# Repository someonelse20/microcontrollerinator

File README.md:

# Microcontrollerinator
Simple custom devboard based on the RP2040 with an integraded 1 cell li-ion charger and Dr. Doofenshmirtz because why not.
This is my first complex pcb and to get my feet wet I mostly followed the example at https://blueprint.hackclub.com/starter-projects/devboard and added the BQ21040DBV battery charger. 

# How To Use
The board has the same pinout as the Raspberry Pi Pico exept ADC_VREF is GPIO23, 3V3_EN is GPIO24, and VSYS is GPIO25. GPIO29_ADC3 monitors the voltage of the battery multiplied by 1.3125 due to the resistor dividor. Pressing the switch will put the RP2040 into boot mode so it can be programed. The VBUS pin will output the current power supply voltage which will be 5v when plugged in but will be the direct battery voltage when unplugged. The battery pin headder has three pins, two for power and one for a thermistor to monitor temperature. The thermistor can be left hanging but there is a solder pad that enables a pull up resistor which is recomended in the charger datasheet.

# Schematic

# PCB

# Ordering
This bom file, the cpl position file, and the gerber zip files are in the production folder and formated to be orederd from https://jlcpcb.com/. The positions file needs to be edited a bit and there isn't an option to export the updated cpl file for JLCPCB so edit as show in the picture below. The USB header goes down a little, U2 pin 1 goes to the bottom left, U3 pin 1 goes to the top left, U4 pin 1 goes to the bottom left, and Q1 pin 1 goes to the top left.
| Id    | Designator                          | Footprint                                   | Quantity | Comment                     | Lcsc part |
| :---- | :---------------------------------- | :------------------------------------------ | :------- | :-------------------------- | :-------- |
| 1     | Y1                                  | Crystal_SMD_3225-4Pin_3.2x2.5mm             | 1        | 12MHz                       | C9002     |
| 2     | SW1                                 | SW_Push_SPST_NO_Alps_SKRK                   | 1        | SW_Push                     | C720477   |
| 3     | C16,C15                             | C_0402_1005Metric                           | 2        | 33pF                        | C1562     |
| 4     | C5,C3,C4,C8,C2,C11,C9,C12,C6,C7,C17 | C_0402_1005Metric                           | 11       | 0.1uF                       | C1525     |
| 5     | J4,J5                               | PinHeader_1x03_P2.54mm_Vertical             | 2        | Conn_01x03                  |           |
| 6     | R6,R11,R9,R5                        | R_0402_1005Metric                           | 4        | 1K                          | C11702    |
| 7     | R2,R1                               | R_0402_1005Metric                           | 2        | 5.1K                        | C25905    |
| 8     | U2                                  | SOT-23                                      | 1        | MCP1700x-330xxTT            | C39051    |
| 9     | C14,C13                             | C_0603_1608Metric                           | 2        | 10uF                        | C19702    |
| 10    | C10,C1,C19,C18                      | C_0402_1005Metric                           | 4        | 1uF                         | C52923    |
| 11    | J1                                  | USB_C_Receptacle_HRO_TYPE-C-31-M-12         | 1        | USB_C_Receptacle_USB2.0_14P | C165948   |
| 12    | U3                                  | Winbond_USON-8-1EP_3x2mm_P0.5mm_EP0.2x1.6mm | 1        | W25Q128JVS                  | C2843335  |
| 13    | D2                                  | LED_0603_1608Metric                         | 1        | LED                         | C2290     |
| 14    | U4                                  | SOT-23-6                                    | 1        | BQ21040DBV                  | C202311   |
| 15    | R8                                  | R_0402_1005Metric                           | 1        | 1.5K                        | C25867    |
| 16    | R12                                 | R_0402_1005Metric                           | 1        | 3.2K                        | C705066   |
| 17    | U1                                  | QFN-56-1EP_7x7mm_P0.4mm_EP3.2x3.2mm         | 1        | RP2040                      | C2040     |
| 18    | D1                                  | D_0402_1005Metric                           | 1        | D_Schottky                  | C28646371 |
| 19    | Q1                                  | SOT-23                                      | 1        | AO3401A                     | C15127    |
| 20    | R4,R3                               | R_0402_1005Metric                           | 2        | 27K                         | C11896    |
| 21    | R10,R7                              | R_0402_1005Metric                           | 2        | 10K                         | C25744    |
| 22    | J3,J2                               | PinHeader_1x20_P2.54mm_Vertical             | 2        | Conn_01x20                  |           |

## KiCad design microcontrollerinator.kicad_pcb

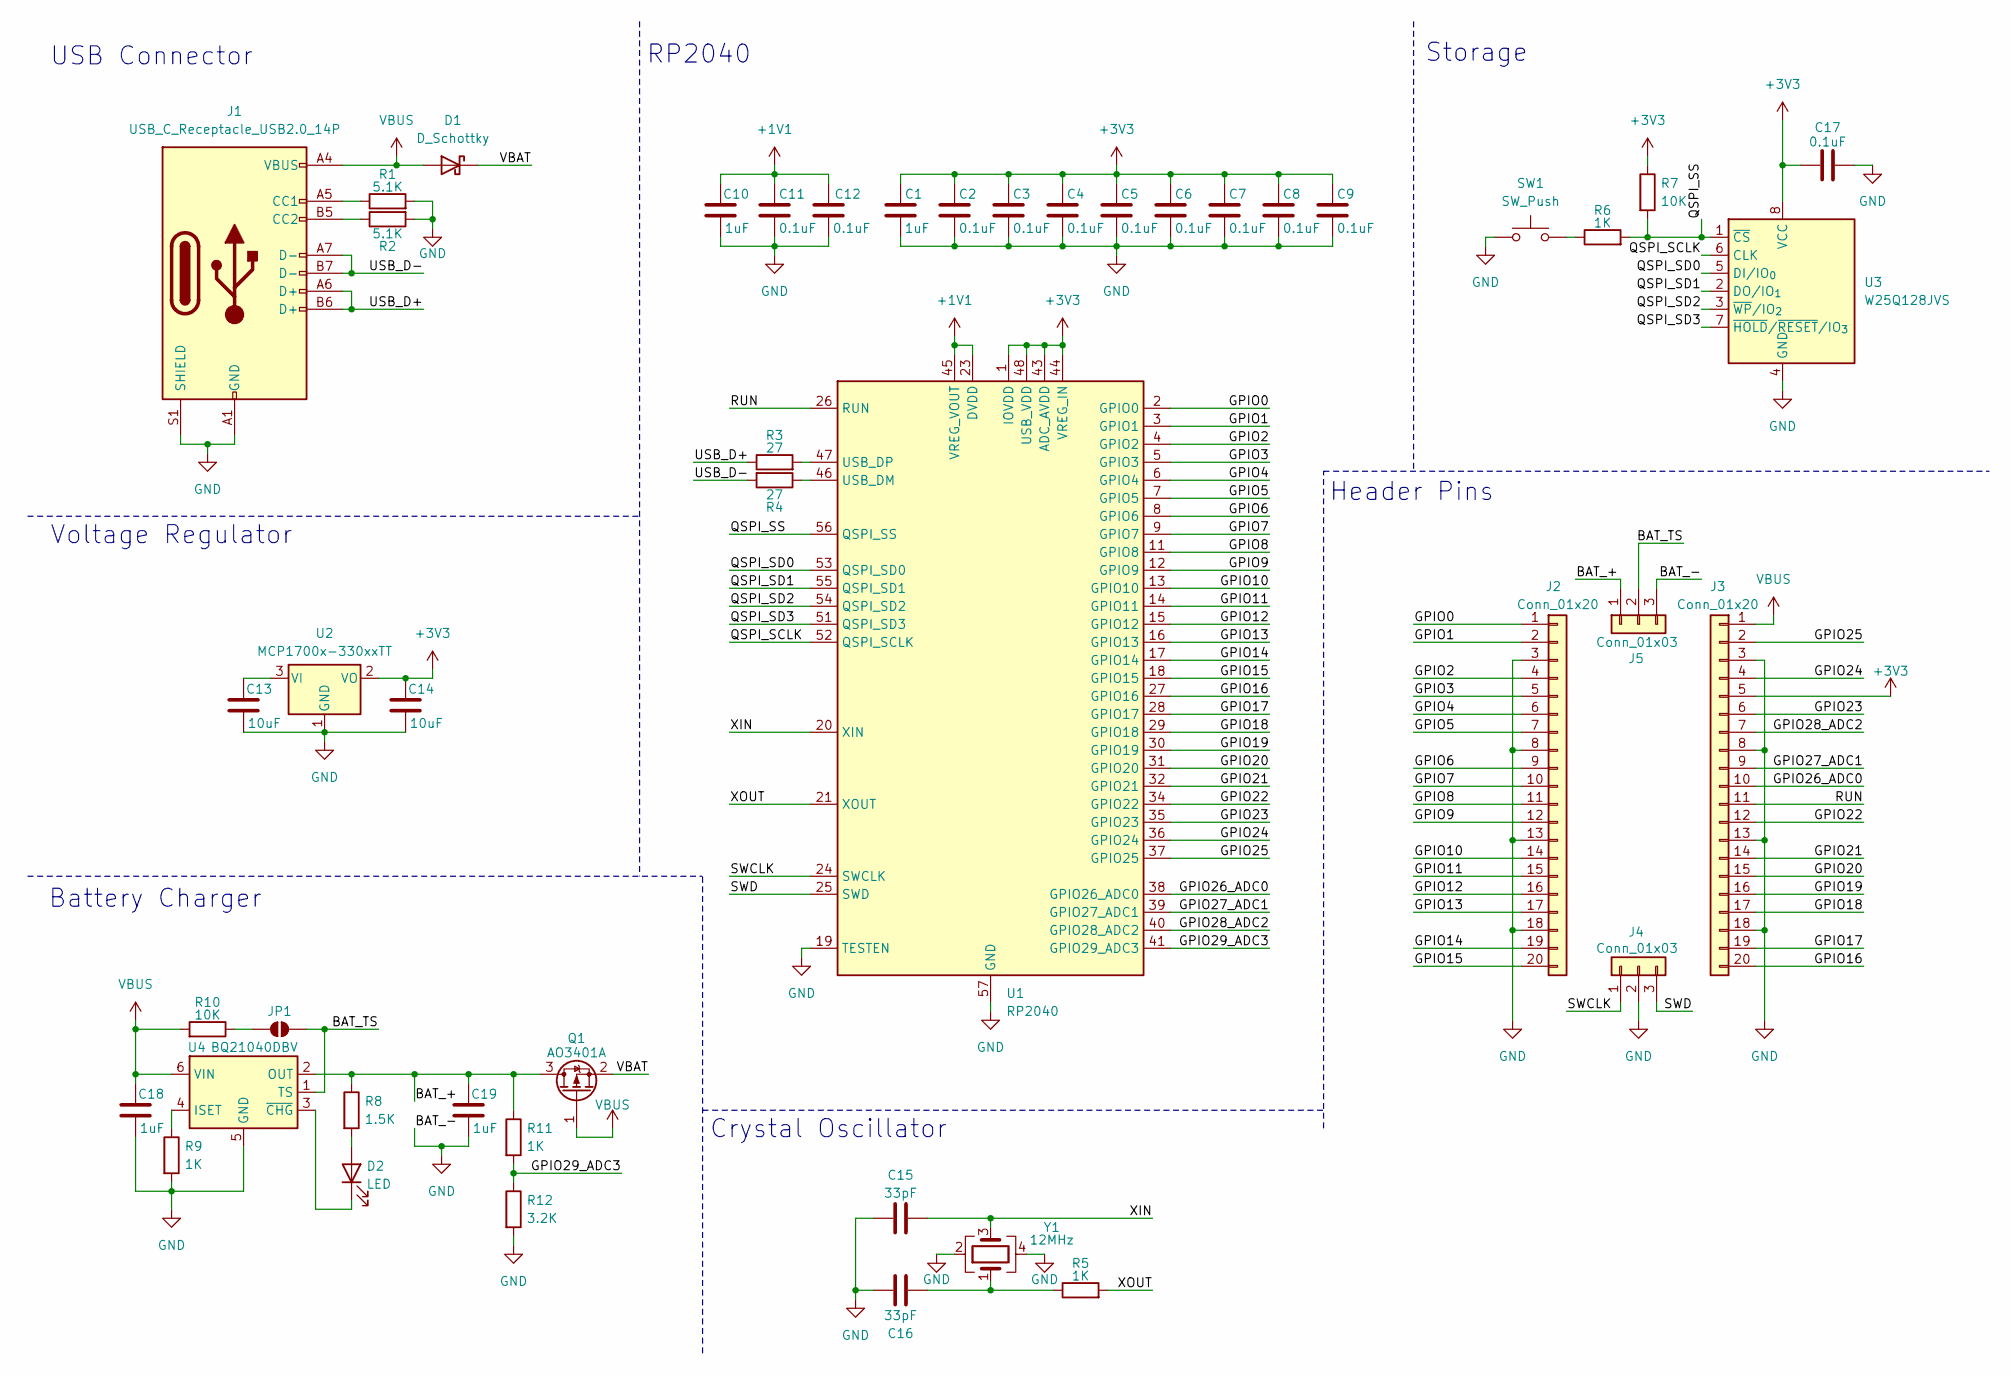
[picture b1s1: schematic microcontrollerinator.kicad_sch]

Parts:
C1, C10, C18, C19: 1uF; C_0402_1005Metric
C2, C3, C4, C5, C6, C7, C8, C9, C11, C12, C17: 0.1uF; C_0402_1005Metric
C13, C14: 10uF; C_0603_1608Metric
C15, C16: 33pF; C_0402_1005Metric
D1: D_Schottky; D_0402_1005Metric
D2: LED; LED_0603_1608Metric
J1: USB_C_Receptacle_USB2.0_14P; USB_C_Receptacle_HRO_TYPE-C-31-M-12
J2, J3: Conn_01x20; PinHeader_1x20_P2.54mm_Vertical
J4, J5: Conn_01x03; PinHeader_1x03_P2.54mm_Vertical
JP1: SolderJumper_2_Open; SolderJumper-2_P1.3mm_Open_RoundedPad1.0x1.5mm
Q1: AO3401A; SOT-23
R1, R2: 5.1K; R_0402_1005Metric
R3, R4: 27; R_0402_1005Metric
R5, R6, R9, R11: 1K; R_0402_1005Metric
R7, R10: 10K; R_0402_1005Metric
R8: 1.5K; R_0402_1005Metric
R12: 3.2K; R_0402_1005Metric
SW1: SW_Push; SW_Push_SPST_NO_Alps_SKRK
U1: RP2040; QFN-56-1EP_7x7mm_P0.4mm_EP3.2x3.2mm
U2: MCP1700x-330xxTT; SOT-23
U3: W25Q128JVS; Winbond_USON-8-1EP_3x2mm_P0.5mm_EP0.2x1.6mm
U4: BQ21040DBV; SOT-23-6
Y1: 12MHz; Crystal_SMD_3225-4Pin_3.2x2.5mm

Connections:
+1V1: C10.1, C11.1, C12.1, U1.23 (DVDD), U1.45 (VREG_VOUT), U1.50 (DVDD)
+3V3: C1.1, C2.1, C3.1, C4.1, C5.1, C6.1, C7.1, C8.1, C9.1, C14.1, C17.1, J3.5, R7.1, U1.1 (IOVDD), U1.10 (IOVDD), U1.22 (IOVDD), U1.33 (IOVDD), U1.42 (IOVDD), U1.43 (ADC_AVDD), U1.44 (VREG_IN), U1.48 (USB_VDD), U1.49 (IOVDD), U2.2 (VO), U3.8 (VCC)
/BAT_+: C19.1, J5.1, Q1.3 (D), R8.1, R11.1, U4.2 (OUT)
/BAT_TS: J5.2, JP1.2 (B), U4.1 (TS)
/GPIO0: J2.1, U1.2 (GPIO0)
/GPIO1: J2.2, U1.3 (GPIO1)
/GPIO2: J2.4, U1.4 (GPIO2)
/GPIO3: J2.5, U1.5 (GPIO3)
/GPIO4: J2.6, U1.6 (GPIO4)
/GPIO5: J2.7, U1.7 (GPIO5)
/GPIO6: J2.9, U1.8 (GPIO6)
/GPIO7: J2.10, U1.9 (GPIO7)
/GPIO8: J2.11, U1.11 (GPIO8)
/GPIO9: J2.12, U1.12 (GPIO9)
/GPIO10: J2.14, U1.13 (GPIO10)
/GPIO11: J2.15, U1.14 (GPIO11)
/GPIO12: J2.16, U1.15 (GPIO12)
/GPIO13: J2.17, U1.16 (GPIO13)
/GPIO14: J2.19, U1.17 (GPIO14)
/GPIO15: J2.20, U1.18 (GPIO15)
/GPIO16: J3.20, U1.27 (GPIO16)
/GPIO17: J3.19, U1.28 (GPIO17)
/GPIO18: J3.17, U1.29 (GPIO18)
/GPIO19: J3.16, U1.30 (GPIO19)
/GPIO20: J3.15, U1.31 (GPIO20)
/GPIO21: J3.14, U1.32 (GPIO21)
/GPIO22: J3.12, U1.34 (GPIO22)
/GPIO23: J3.6, U1.35 (GPIO23)
/GPIO24: J3.4, U1.36 (GPIO24)
/GPIO25: J3.2, U1.37 (GPIO25)
/GPIO26_ADC0: J3.10, U1.38 (GPIO26_ADC0)
/GPIO27_ADC1: J3.9, U1.39 (GPIO27_ADC1)
/GPIO28_ADC2: J3.7, U1.40 (GPIO28_ADC2)
/GPIO29_ADC3: R11.2, R12.1, U1.41 (GPIO29_ADC3)
/QSPI_SCLK: U1.52 (QSPI_SCLK), U3.6 (CLK)
/QSPI_SD0: U1.53 (QSPI_SD0), U3.5 (DI/IO_{0})
/QSPI_SD1: U1.55 (QSPI_SD1), U3.2 (DO/IO_{1})
/QSPI_SD2: U1.54 (QSPI_SD2), U3.3 (~WP/IO_{2})
/QSPI_SD3: U1.51 (QSPI_SD3), U3.7 (~HOLD/~RESET/IO_{3})
/QSPI_SS: R6.2, R7.2, U1.56 (QSPI_SS), U3.1 (~CS)
/RUN: J3.11, U1.26 (RUN)
/SWCLK: J4.1, U1.24 (SWCLK)
/SWD: J4.3, U1.25 (SWD)
/USB_D+: J1.A6 (D+), J1.B6 (D+), R3.1
/USB_D-: J1.A7 (D-), J1.B7 (D-), R4.2
/VBAT: D1.1 (K), Q1.2 (S)
/XIN: C15.2, U1.20 (XIN), Y1.3
/XOUT: R5.2, U1.21 (XOUT)
GND: C1.2, C2.2, C3.2, C4.2, C5.2, C6.2, C7.2, C8.2, C9.2, C10.2, C11.2, C12.2, C13.2, C14.2, C15.1, C16.2, C17.2, C18.2, C19.2, J1.A1 (GND), J1.A12 (GND), J1.B1 (GND), J1.B12 (GND), J1.S1 (SHIELD), J2.3, J2.8, J2.13, J2.18, J3.3, J3.8, J3.13, J3.18, J4.2, J5.3, R1.2, R2.2, R9.2, R12.2, SW1.1, U1.19 (TESTEN), U1.57 (GND), U2.1 (GND), U3.4 (GND), U4.5 (GND), Y1.2, Y1.4
unnamed: C16.1, R5.1, Y1.1
unnamed: D2.2 (A), R8.2
unnamed: D2.1 (K), U4.3 (~CHG)
unnamed: J1.A5 (CC1), R1.1
unnamed: J1.B5 (CC2), R2.1
unnamed: JP1.1 (A), R10.1
unnamed: R6.1, SW1.2
unnamed: R4.1, U1.46 (USB_DM)
unnamed: R3.2, U1.47 (USB_DP)
unnamed: C13.1, U2.3 (VI)
unnamed: R9.1, U4.4 (ISET)
VBUS: C18.1, D1.2 (A), J1.A4 (VBUS), J1.A9 (VBUS), J1.B4 (VBUS), J1.B9 (VBUS), J3.1, Q1.1 (G), R10.2, U4.6 (VIN)

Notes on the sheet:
Voltage Regulator
Header Pins
Crystal Oscillator
Battery Charger
Storage
RP2040
USB Connector

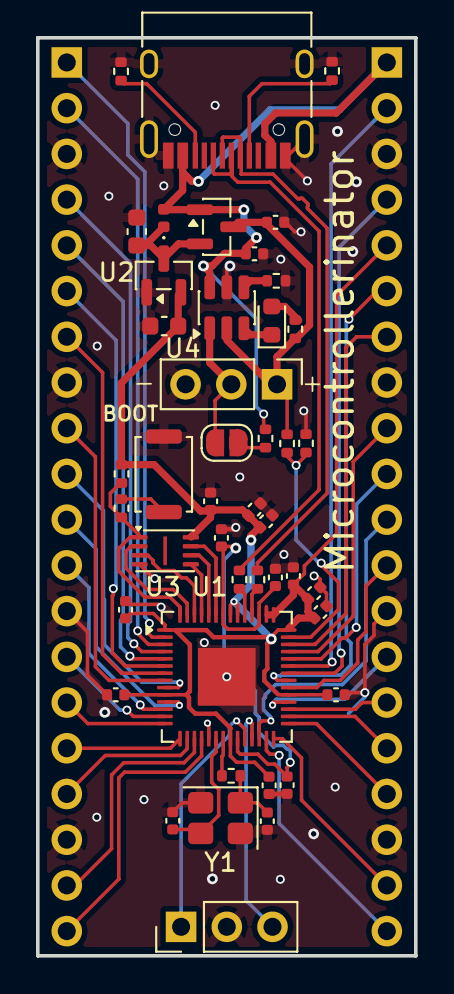
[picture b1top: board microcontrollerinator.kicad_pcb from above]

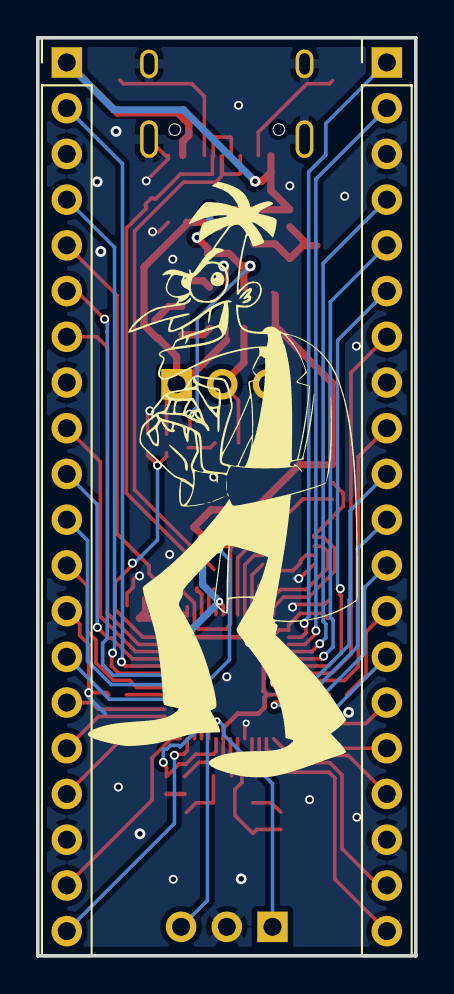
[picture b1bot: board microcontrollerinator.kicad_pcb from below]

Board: 2 copper layers, 21.0 x 51.0 mm, 46 parts (2 on the bottom side), 61 nets.

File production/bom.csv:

"Id","Designator","Footprint","Quantity","Comment","LCSC Part #",
1,"Y1","Crystal_SMD_3225-4Pin_3.2x2.5mm",1,"12MHz",C9002,,
2,"SW1","SW_Push_SPST_NO_Alps_SKRK",1,"SW_Push",C720477,,
3,"C16,C15","C_0402_1005Metric",2,"33pF",C1562,,
4,"C5,C3,C4,C8,C2,C11,C9,C12,C6,C7,C17","C_0402_1005Metric",11,"0.1uF",C1525,,
5,"J4,J5","PinHeader_1x03_P2.54mm_Vertical",2,"Conn_01x03",,,
6,"R6,R11,R9,R5","R_0402_1005Metric",4,"1K",C11702,,
7,"R2,R1","R_0402_1005Metric",2,"5.1K",C25905,,
8,"U2","SOT-23",1,"MCP1700x-330xxTT",C39051,,
9,"C14,C13","C_0603_1608Metric",2,"10uF",C19702,,
10,"C10,C1,C19,C18","C_0402_1005Metric",4,"1uF",C52923,,
11,"J1","USB_C_Receptacle_HRO_TYPE-C-31-M-12",1,"USB_C_Receptacle_USB2.0_14P",C165948,,
12,"U3","Winbond_USON-8-1EP_3x2mm_P0.5mm_EP0.2x1.6mm",1,"W25Q128JVS",C2843335,,
13,"D2","LED_0603_1608Metric",1,"LED",C2290,,
14,"U4","SOT-23-6",1,"BQ21040DBV",C202311,,
15,"R8","R_0402_1005Metric",1,"1.5K",C25867,,
16,"R12","R_0402_1005Metric",1,"3.2K",C705066,,
17,"U1","QFN-56-1EP_7x7mm_P0.4mm_EP3.2x3.2mm",1,"RP2040",C2040,,
18,"D1","D_0402_1005Metric",1,"D_Schottky",C28646371,,
19,"Q1","SOT-23",1,"AO3401A",C15127,,
20,"R4,R3","R_0402_1005Metric",2,"27K",C11896,,
21,"R10,R7","R_0402_1005Metric",2,"10K",C25744,,
22,"J3,J2","PinHeader_1x20_P2.54mm_Vertical",2,"Conn_01x20",,,

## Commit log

2026-02-06 first draft of schematic
2026-02-06 routing pcb
2026-02-07 finished routing pcb
2026-02-07 added production files
2026-02-09 fixed 3d model
2026-02-09 checked pcb
2026-02-11 finished board
2026-02-11 cleaning up
2026-02-11 added .step file
2026-02-11 cleaned up schematic
2026-02-11 added example code
2026-02-11 removed uneeded files
2026-03-04 building c example
2026-03-05 fixed example script
2026-03-05 fixed pcb
2026-03-05 added battery drain script
2026-03-05 added batteryDrain.c
2026-03-10 added python code
2026-03-10 added c code
